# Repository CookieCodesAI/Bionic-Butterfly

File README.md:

# Bionic-Butterfly
A butterfly-like drone that can be manually controlled from your computer.

## Why I made this project
For a while now, I've been wanted to create bigger hardware projects than the ones that I had been making previously. I wanted to make an aesthetic project that would make me go beyond my limits. Making a drone was the first idea that came to mind, and with the help of my Instagram feed, I got inspired to make a butterfly drone, leading to the creation of this project!

### 3D model of whole project

The wings will be made with flower paper and carbon fiber to make sure that they don't weigh too much. Additionally, the wings will be connected to the servo horns with a connector that I will make and mold to make sure that it fits perfectly.  

### 3D model of main body with Servos and Raspberry Pi Pico

The PCB will be able to fit in the gap in the middle of the body. The servos will be placed on the angled sides of the main body and the wires will be connected as shown in the wiring diagram. The 2S LiPo battery is the yellow rectangle that was measured with the dimensions of the LiPo battery in my BOM. 

### Wiring Diagram

### Schematics

### Custom PCB

- Boost Converter 
- LiPo Battery Charger 
- LiPo Battery Port
- Raspberry Pi Pico W
- Servo Header Pins for Easy Connection

### BOM
|Name                      |Quantity|Link                                                                                                                                                                                                                                                                                                                                                                                                                                                                                                                                                                     |Total Cost|Distributor|Purpose                                      |Footprint                                                 |Value             |
|--------------------------|--------|-------------------------------------------------------------------------------------------------------------------------------------------------------------------------------------------------------------------------------------------------------------------------------------------------------------------------------------------------------------------------------------------------------------------------------------------------------------------------------------------------------------------------------------------------------------------------|----------|-----------|---------------------------------------------|----------------------------------------------------------|------------------|
|PTK 7462W                 |2       |https://www.amazon.com/7462W-Waterproof-Servo-Motor-Metal/dp/B0FS6RFS5T/ref=sr_1_5?crid=1ZB1W7OBY92AH&dib=eyJ2IjoiMSJ9.pcNsqKatkWgVfKurDM9eHL21UShPA7q6GXI9fo14TvFABX6NUw60A4k6qXJAddcV1jaM5bD_ihRYej-b-Lx6ysEhNUEZTNV9GKiLSC5LTDlzWu8q_CSUwAYdmiKw9ZnP_5f4FPnJ8-klUCwh87w4VGMC84lR6LUw1btxYo-F4Utq2s6qgV90yjv_KvqzCP6eqCl0Q55bP6fYXsnqbciufLyxbyqG7qBHzq3PKEA_Hxg.YU3fGmyR3zlSbmNrTrl-zQXaLwKUesFVOlDi5g06fR0&dib_tag=se&keywords=PTK&qid=1777691727&sprefix=ptk%2Caps%2C100&sr=8-5&th=1                                                                                |27.54     |Amazon     |Motors for the wings                         |                                                          |                  |
|2s LiPo Battery           |1       |https://www.amazon.com/Tattu-300mAh-7-6V-Battery-JST-PHR/dp/B097BVFYLX/ref=sr_1_13?crid=2ZJ76ZHNRXD50&dib=eyJ2IjoiMSJ9.9CM4Ph0ZcswTXalgAhFYgxwOa2_mpoX-U946yyTZ0te5qCaS84KWHWp3iqs04T6AywbCIiWH9XYEyJsVoqdngsM1OFrK0zdpFP-iEN38fjmUQdWUuZeBDpqbK9Beafcs4k2VeU3F8SMT-0VUStvHtMt6wPazmiYsP0k07IPMTnAapAwwXfVFp9KGYUJMYu8L33jbZLZ2P7qx-fH6v0T9QAhEeHj8Ldyvm-nWqyEeHXX5hSPaQ8l0aw3_RJRse0mbgUpd3e6yb-LZ_qXxl4jWPsdYEYjkYCi52l_5oWrDBoY.Pv-Sbm1U3Sdy41Tj8nN-aCbiLgHkswAEGGEC4bIILGc&dib_tag=se&keywords=2s+7.6+v+lipo&qid=1777692124&sprefix=2s+7.6+v+lipo%2Caps%2C91&sr=8-13 |9.99      |Amazon     |Power for microcontroller and motors         |                                                          |                  |
|Custom PCB                |5       |https://cart.jlcpcb.com/quote?spm=jlcpcb.Public.2006&spm=Jlcpcb.Instantquote&_t=1777938855701&up_spm=Jlcpcb.Loginpage.1003                                                                                                                                                                                                                                                                                                                                                                                                                                               |2         |JCLPCB     |Manufacturing PCB for custom microcontroller |                                                          |                  |
|A1                        |1       |https://www.adafruit.com/product/5526?gad_source=1&gad_campaignid=23438252138&gbraid=0AAAAADx9JvRU8AUIiT14w9XCblnLEohNW&gclid=Cj0KCQjwh-HPBhCIARIsAC0p3cexzLr-P9xc99KU2w8qJSMWC_1im0GuzYcRuyEFFIox6lz7J-F-BzQaAi_6EALw_wcB                                                                                                                                                                                                                                                                                                                                               |6         |Adafruit   |Microcontroller                              |Module:RaspberryPi_Pico_W_SMD_HandSolder                  |RaspberryPi_Pico_W|
|C_3V3,C_BAT1              |2       |https://www.digikey.com/en/products/detail/w%C3%BCrth-elektronik/860020473008/5727062                                                                                                                                                                                                                                                                                                                                                                                                                                                                                    |0.26      |DigiKey    |PCB component                                |Capacitor_THT:CP_Radial_D5.0mm_P2.50mm                    |100uF             |
|C_3V3_bypass1,C_5V_bypass1|2       |https://www.digikey.com/en/products/detail/samsung-electro-mechanics/CL05B104KP5VPNC/20498482                                                                                                                                                                                                                                                                                                                                                                                                                                                                            |0.2       |DigiKey    |PCB component                                |Capacitor_SMD:C_0402_1005Metric                           |100nF             |
|C_5V1                     |1       |https://www.digikey.com/en/products/detail/kemet/ESK107M025AC3AA/2712507                                                                                                                                                                                                                                                                                                                                                                                                                                                                                                 |0.2       |DigiKey    |PCB component                                |Capacitor_THT:CP_Radial_D5.0mm_P2.00mm                    |100uF             |
|D1                        |1       |http://digikey.com/en/products/detail/onsemi/SS14/965474                                                                                                                                                                                                                                                                                                                                                                                                                                                                                                                 |0.44      |DigiKey    |PCB component                                |Diode_SMD:D_SMA                                           |SS14              |
|J_BAT1                    |1       |https://www.digikey.com/en/products/detail/jst-sales-america-inc/S2B-PH-K-S/926626                                                                                                                                                                                                                                                                                                                                                                                                                                                                                       |0.11      |DigiKey    |PCB component                                |Connector_JST:JST_PH_S2B-PH-K_1x02_P2.00mm_Horizontal     |Conn_01x02_Socket |
|J_DBG1                    |1       |https://www.digikey.com/en/products/detail/sullins-connector-solutions/GRPB031VWVN-RC/1786439                                                                                                                                                                                                                                                                                                                                                                                                                                                                            |0.21      |DigiKey    |PCB component                                |Connector_PinHeader_1.27mm:PinHeader_1x03_P1.27mm_Vertical|Conn_01x03_Pin    |
|J_EXT1                    |1       |https://www.digikey.com/en/products/detail/w%C3%BCrth-elektronik/61300811121/4846839                                                                                                                                                                                                                                                                                                                                                                                                                                                                                     |0.4       |DigiKey    |PCB component                                |Connector_PinHeader_2.54mm:PinHeader_1x08_P2.54mm_Vertical|Conn_01x08_Pin    |
|J_SRV1,J_SRV2             |2       |https://www.digikey.com/en/products/detail/w%C3%BCrth-elektronik/61300311121/4846825                                                                                                                                                                                                                                                                                                                                                                                                                                                                                     |0.26      |DigiKey    |PCB component                                |Connector_PinHeader_2.54mm:PinHeader_1x03_P2.54mm_Vertical|Conn_01x03_Pin    |
|L1                        |1       |https://www.digikey.com/en/products/detail/taiyo-yuden/LCXND3030QKT4R7MNG/22251951                                                                                                                                                                                                                                                                                                                                                                                                                                                                                       |0.27      |DigiKey    |PCB component                                |Inductor_SMD:L_Taiyo-Yuden_NR-30xx                        |4.7uH             |
|LED_CHG1                  |1       |https://www.digikey.com/en/products/detail/sunled/XZFRA53FVC-1/28246155                                                                                                                                                                                                                                                                                                                                                                                                                                                                                                  |0.86      |DigiKey    |PCB component                                |LED_SMD:LED_0603_1608Metric                               |LED               |
|MCP73831                  |1       |https://www.digikey.com/en/products/detail/microchip-technology/MCP73831T-2ACI-OT/964301                                                                                                                                                                                                                                                                                                                                                                                                                                                                                 |0.76      |DigiKey    |PCB component                                |Package_TO_SOT_SMD:SOT-23-5                               |                  |
|MT3608                    |1       |https://www.lcsc.com/product-detail/C84817.html?s_z=n_q_MT3608&spm=wm.ssy.bg.0.xh&lcsc_vid=RlEIUldTRlENVVQFEQVeAwADT1VXA1ECQldXUgFTEVExVlNRQFhdUFZXQVdWVDsOAxUeFF5JWBYZEEoKFBINSQcJGk4%3D                                                                                                                                                                                                                                                                                                                                                                                |0.79      |LCSC       |PCB component                                |Package_TO_SOT_SMD:SOT-23-6                               |                  |
|R_FB1                     |1       |https://www.digikey.com/en/products/detail/yageo/RC0402FR-07100KL/726526                                                                                                                                                                                                                                                                                                                                                                                                                                                                                                 |0.1       |DigiKey    |PCB component                                |Resistor_SMD:R_0402_1005Metric                            |100k              |
|R_FB2                     |1       |https://www.digikey.com/en/products/detail/yageo/RC0402FR-0736KL/726598                                                                                                                                                                                                                                                                                                                                                                                                                                                                                                  |0.1       |DigiKey    |PCB component                                |Resistor_SMD:R_0402_1005Metric                            |36k               |
|R_LED1                    |1       |https://www.digikey.com/en/products/detail/yageo/RC0402FR-071KL/726513                                                                                                                                                                                                                                                                                                                                                                                                                                                                                                   |0.1       |DigiKey    |PCB component                                |Resistor_SMD:R_0402_1005Metric                            |1k                |
|R_PROG1                   |1       |https://www.digikey.com/en/products/detail/yageo/RC0402FR-072KL/2827565                                                                                                                                                                                                                                                                                                                                                                                                                                                                                                  |0.1       |DigiKey    |PCB component                                |Resistor_SMD:R_0402_1005Metric                            |2k                |
|R_SRV1,R_SRV2             |2       |https://www.digikey.com/en/products/detail/yageo/RC0402FR-0747RL/2827566                                                                                                                                                                                                                                                                                                                                                                                                                                                                                                 |0.2       |DigiKey    |PCB component                                |Resistor_SMD:R_0402_1005Metric                            |47                |
|SW1                       |1       |https://www.digikey.com/en/products/detail/c-k/OS102011MS2QN1/411602                                                                                                                                                                                                                                                                                                                                                                                                                                                                                                     |0.73      |DigiKey    |PCB component                                |Button_Switch_THT:SW_Slide_SPDT_Straight_CK_OS102011MS2Q  |SW_SPDT           |

### Total materials cost: $51.62

### Materials that are needed that I did not include in the BOM (Since I already have them)
- 1.00 mm carbon fiber
- Some type of thin flower/kite paper

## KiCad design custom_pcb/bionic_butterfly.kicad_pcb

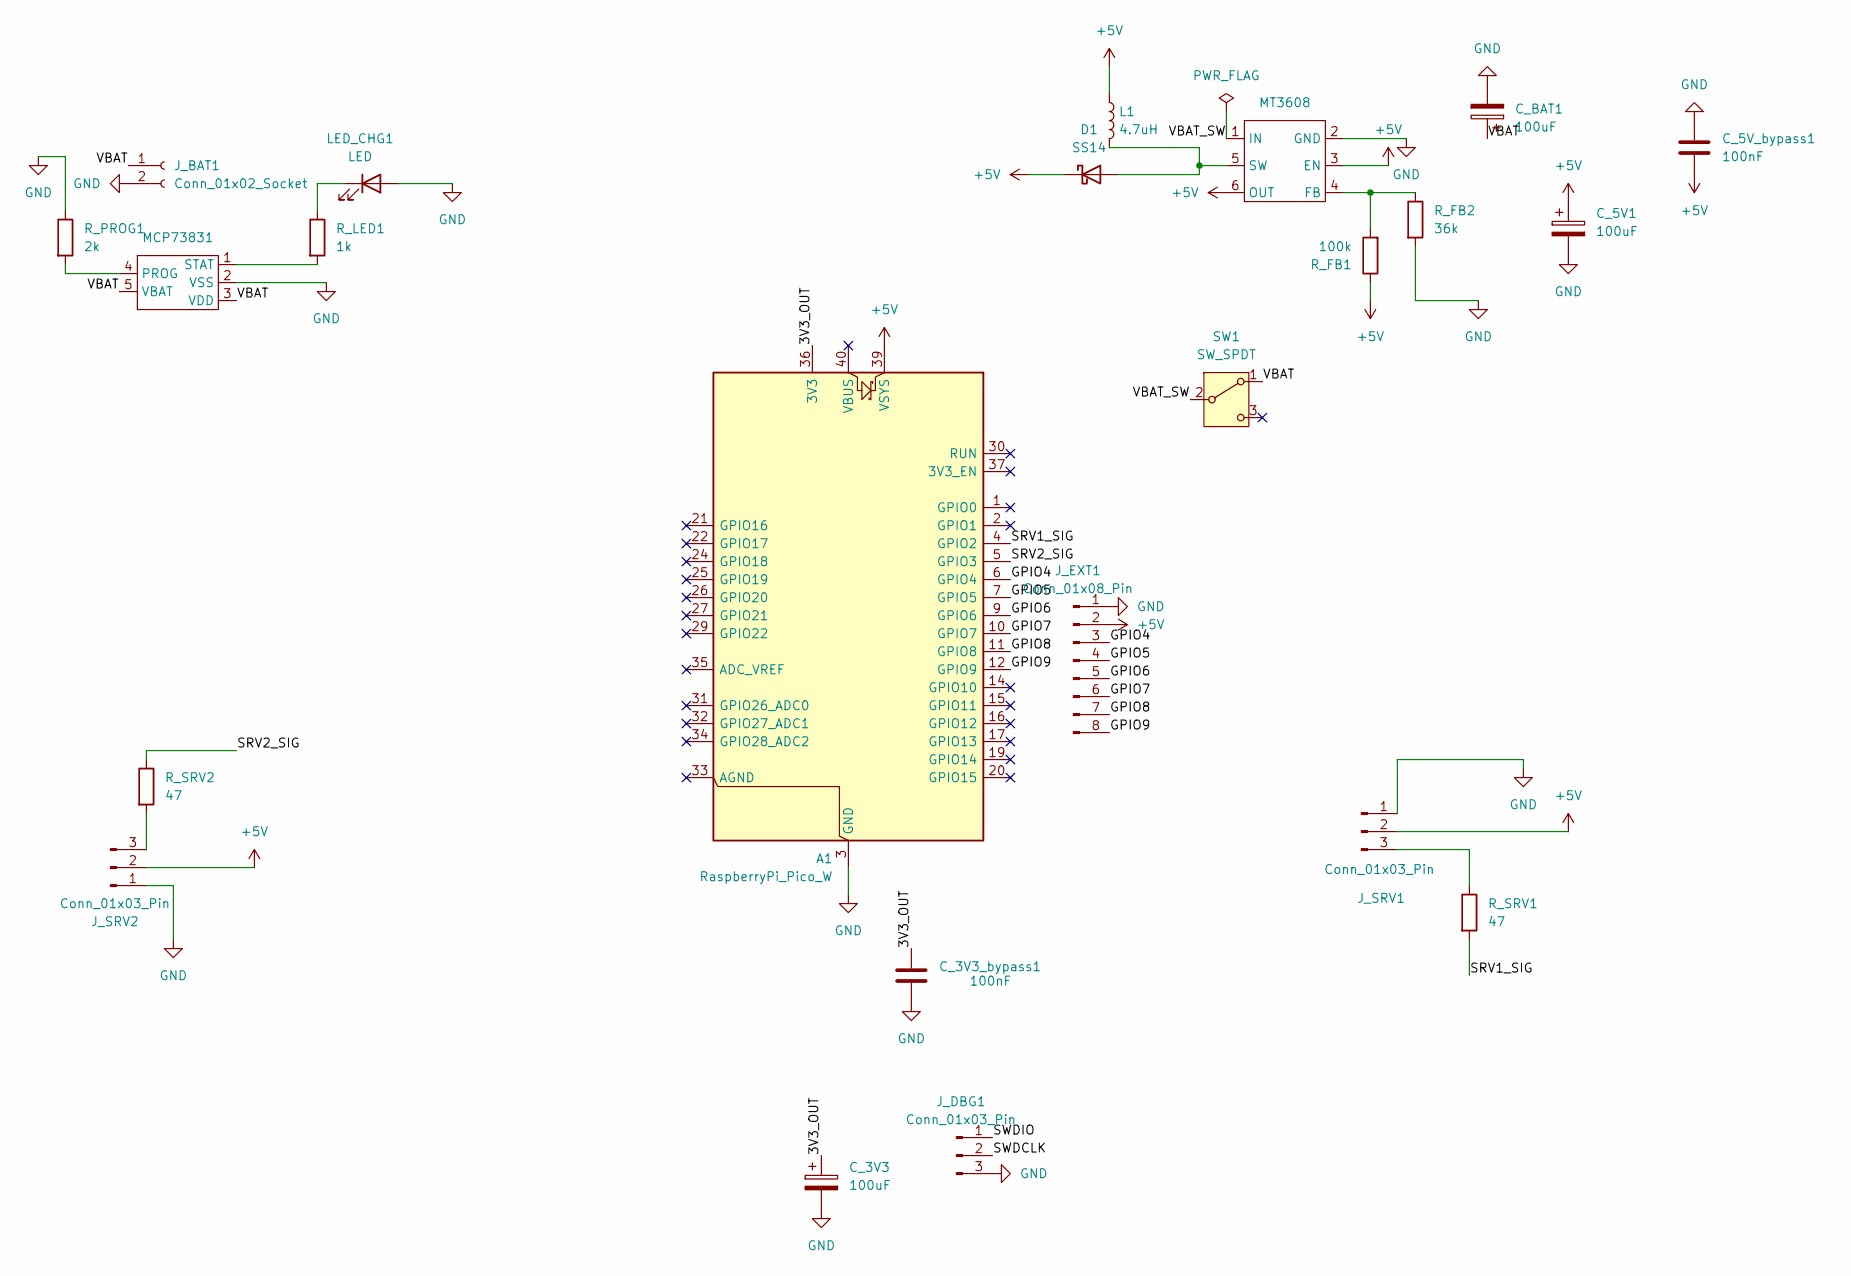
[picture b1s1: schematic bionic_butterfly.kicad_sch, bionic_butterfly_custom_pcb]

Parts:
A1: RaspberryPi_Pico_W; RaspberryPi_Pico_W_SMD_HandSolder
C_3V3: 100uF; CP_Radial_D5.0mm_P2.50mm
C_3V3_bypass1, C_5V_bypass1: 100nF; C_0402_1005Metric
C_5V1: 100uF; CP_Radial_D5.0mm_P2.00mm
C_BAT1: 100uF; CP_Radial_D5.0mm_P2.50mm
D1: SS14; D_SMA
J_BAT1: Conn_01x02_Socket; JST_PH_S2B-PH-K_1x02_P2.00mm_Horizontal
J_DBG1: Conn_01x03_Pin; PinHeader_1x03_P1.27mm_Vertical
J_EXT1: Conn_01x08_Pin; PinHeader_1x08_P2.54mm_Vertical
J_SRV1, J_SRV2: Conn_01x03_Pin; PinHeader_1x03_P2.54mm_Vertical
L1: 4.7uH; L_Taiyo-Yuden_NR-30xx
LED_CHG1: LED; LED_0603_1608Metric
MCP73831: SOT-23-5
MT3608: SOT-23-6
R_FB1: 100k; R_0402_1005Metric
R_FB2: 36k; R_0402_1005Metric
R_LED1: 1k; R_0402_1005Metric
R_PROG1: 2k; R_0402_1005Metric
R_SRV1, R_SRV2: 47; R_0402_1005Metric
SW1: SW_SPDT; SW_Slide_SPDT_Straight_CK_OS102011MS2Q

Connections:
+5V: A1.39 (VSYS), C_5V1.1, C_5V_bypass1.2, D1.1 (K), J_EXT1.2, J_SRV1.2, J_SRV2.2, L1.1, MT3608.3 (EN), MT3608.6 (OUT), R_FB1.1
/3V3_OUT: A1.36 (3V3), C_3V3.1, C_3V3_bypass1.1
/GPIO4: A1.6 (GPIO4), J_EXT1.3
/GPIO5: A1.7 (GPIO5), J_EXT1.4
/GPIO6: A1.9 (GPIO6), J_EXT1.5
/GPIO7: A1.10 (GPIO7), J_EXT1.6
/GPIO8: A1.11 (GPIO8), J_EXT1.7
/GPIO9: A1.12 (GPIO9), J_EXT1.8
/SRV1_SIG: A1.4 (GPIO2), R_SRV1.2
/SRV2_SIG: A1.5 (GPIO3), R_SRV2.1
/SWDCLK: J_DBG1.2
/SWDIO: J_DBG1.1
/VBAT: C_BAT1.1, J_BAT1.1, MCP73831.3 (VDD), MCP73831.5 (VBAT), SW1.1 (A)
/VBAT_SW: MT3608.1 (IN), SW1.2 (B)
GND: A1.3 (GND), A1.8 (GND), A1.13 (GND), A1.18 (GND), A1.23 (GND), A1.28 (GND), A1.38 (GND), C_3V3.2, C_3V3_bypass1.2, C_5V1.2, C_5V_bypass1.1, C_BAT1.2, J_BAT1.2, J_DBG1.3, J_EXT1.1, J_SRV1.1, J_SRV2.1, LED_CHG1.2 (A), MCP73831.2 (VSS), MT3608.2 (GND), R_FB2.2, R_PROG1.1
unnamed: D1.2 (A), L1.2, MT3608.5 (SW)
unnamed: J_SRV1.3, R_SRV1.1
unnamed: J_SRV2.3, R_SRV2.2
unnamed: LED_CHG1.1 (K), R_LED1.1
unnamed: MCP73831.4 (PROG), R_PROG1.2
unnamed: MCP73831.1 (STAT), R_LED1.2
unnamed: MT3608.4 (FB), R_FB1.2, R_FB2.1

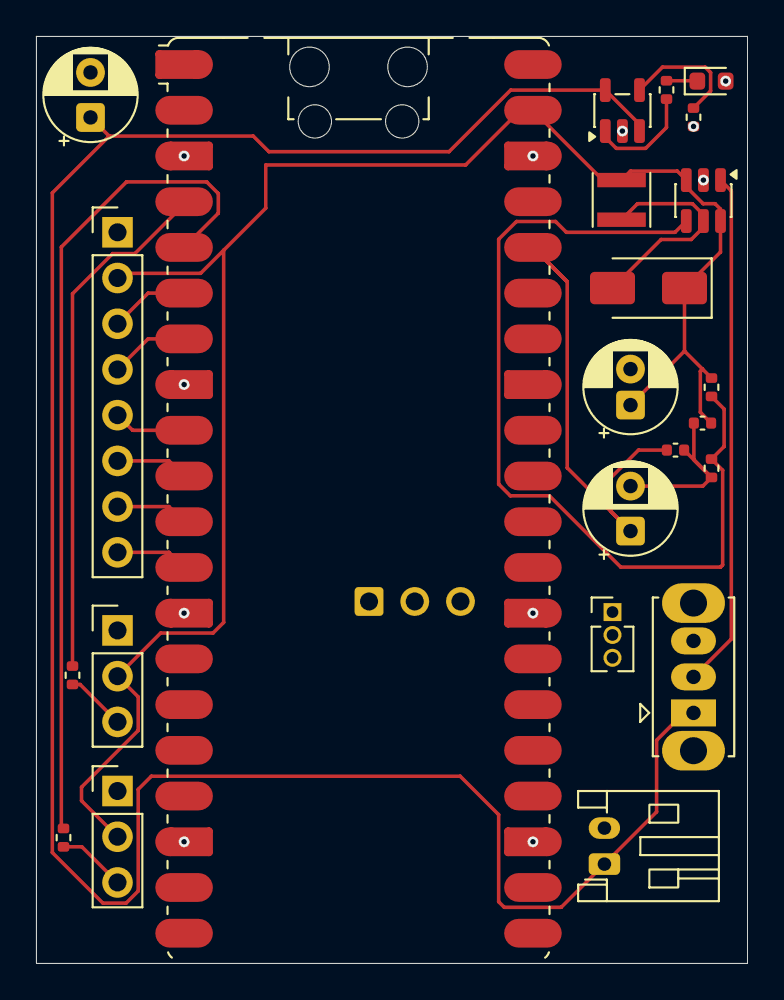
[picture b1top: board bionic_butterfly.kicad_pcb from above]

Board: 2 copper layers, 39.5 x 51.5 mm, 23 parts (0 on the bottom side), 20 nets.

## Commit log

2026-04-22 added 3D model files
2026-04-22 edited README and added images
2026-04-26 added new images and new 3d-models
2026-04-26 added main.py
2026-04-26 edited main.py
2026-04-26 edited readme
2026-04-26 edited readme again
2026-05-05 edited hardware and cad and added BOM
